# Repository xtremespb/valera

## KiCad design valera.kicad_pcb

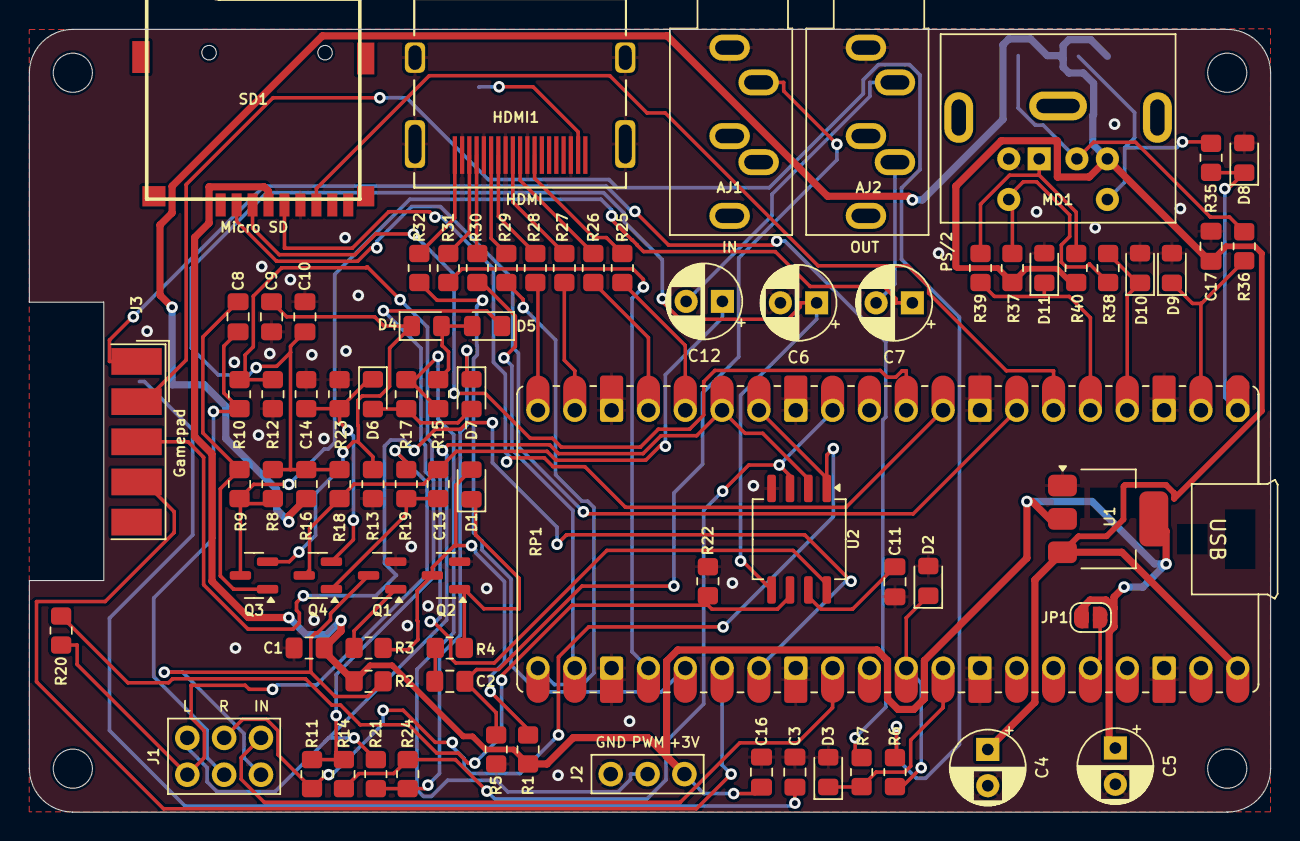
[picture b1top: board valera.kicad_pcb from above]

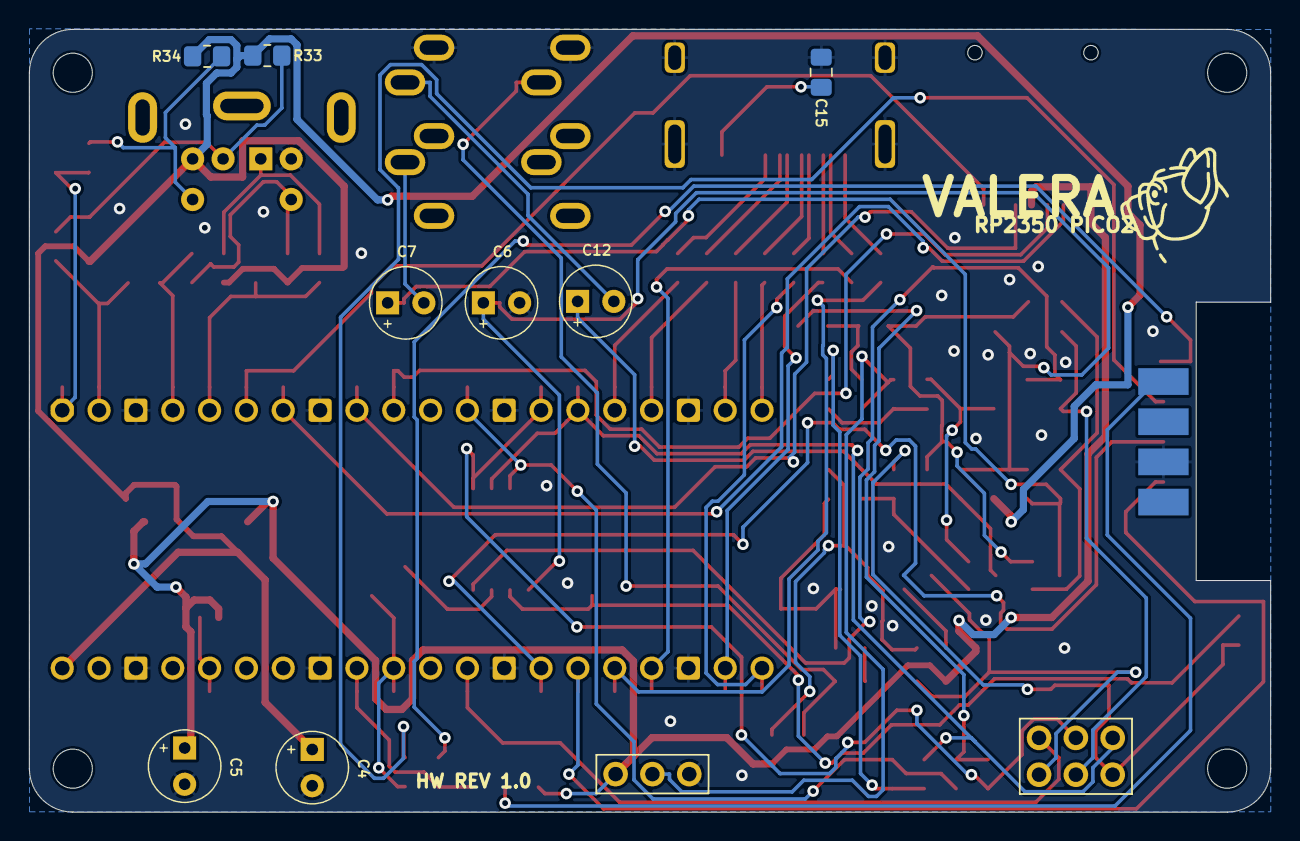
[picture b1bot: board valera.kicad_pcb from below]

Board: 2 copper layers, 85.6 x 54.0 mm, 88 parts (3 on the bottom side), 69 nets.

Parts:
AJ1: Audio IN; Jack_3.5mm
AJ2: Audio OUT; Jack_3.5mm
C1, C2, C9, C10, C15, C16: 100n; C_0805
C3: 0.1u; C_0805
C4, C5, C6, C7, C12: 10u; C_Radial
C8, C11: 1u; C_0805
C13: 1u; R_0805
C14: 100n; R_0805
C17: 10u; C_0805
D1, D4, D5, D6, D7: 4148; D_0805
D2, D3, D8, D9, D10, D11: 3V3; D_0805
H1, H2, H3, H4: MountingHole; MountingHole_2.7
HDMI1: HDMI
J1: Audio Jumpers; PinHeader_2x03
J2: PWM Jumper; PinHeader_1x03
J3: JOY-1; DSUB-9_Male_EdgeMount_P2.77mm
JP1: Enable 3V3; S_Jumper
MD1: Mini-DIN-6; Connector_Mini-DIN_Female_6Pin_2rows
Q1, Q2, Q3, Q4: BC850; Q_SOT-23
R1, R3, R4: 10K; R_0805
R2, R6, R7, R8, R12, R18, R22, R33, R34, R37: 1K; R_0805
R5, R13, R35, R36, R38, R39: 100R; R_0805
R9, R19: 100K*; R_0805
R10, R20: 20K; R_0805
R11, R21: 51R; R_0805
R14, R15, R17, R24: 200R; R_0805
R16: 10R; R_0805
R23: 100; R_0805
R25, R26, R27, R28, R29, R30, R31, R32: 270R; R_0805
R40: 1k; R_0805
RP1: Pico 2; Raspberry_Pi_Pico_SMT_THT_MOD_2
SD1: Micro_SD_Card; GCT-MEM2055-00-190-01-A
U1: AMS1117-3.3; SOT-223-3_TabPin2
U2: TDA1387T; SO_4x4

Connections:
+3V3: C1.1, C5.1, C16.2, J2.3, JP1.1 (A), R1.1, R2.1, SD1.4 (VDD), U1.2 (VO)
/3V3_EXT: JP1.2 (B), RP1.36 (3V3)
/AU_DATA: R14.2, R24.2, RP1.12 (GPIO9), U2.3 (DATA)
/AU_LRCK: J1.6, R21.2, RP1.15 (GPIO11), U2.2 (LRCK)
/AU_SCLK: J1.5, R11.2, RP1.14 (GPIO10), U2.1 (SCLK)
/Audio Out/+5VA: C6.1, C10.1, R8.1, R16.1, R18.1, U2.5 (VA)
/Audio Out/L: AJ2.T, C12.2
/Audio Out/R: AJ2.R, C7.2
/CLKN: R25.2, RP1.16 (GPIO12)
/CLKP: R26.2, RP1.17 (GPIO13)
/D0N: R27.2, RP1.19 (GPIO14)
/D0P: R28.2, RP1.20 (GPIO15)
/D1N: R29.2, RP1.21 (GPIO16)
/D1P: R30.2, RP1.22 (GPIO17)
/D2N: R31.2, RP1.24 (GPIO18)
/D2P: R32.2, RP1.25 (GPIO19)
/Gamepad/+5V: C3.1, J3.6
/Gamepad/J1_DATA: J3.2, R6.2
/Gamepad/J2_DATA: J3.1, R7.2
/HDMI/+5V: C15.1, HDMI1.18 (+5V)
/JOY_PIN1: D3.1 (K), R7.1, RP1.32 (GPIO27_ADC1)
/JOY_PIN2: D2.1 (K), R6.1, RP1.31 (GPIO26_ADC0)
/JOY_PIN3: J3.3, RP1.27 (GPIO21)
/JOY_PIN4: J3.4, RP1.26 (GPIO20)
/KB_CLK_3V: D10.1 (K), R38.2, RP1.4 (GPIO2)
/KB_DATA_3V: D11.1 (K), R39.2, RP1.5 (GPIO3)
/LEFT_OUT: C13.1, J1.1, R20.2
/LOAD_IN: J1.4, RP1.29 (GPIO22)
/LOAD_IN_D: J1.3, Q1.3 (C), R2.2
/MS_CLK_3V: D8.1 (K), R35.2, RP1.1 (GPIO0)
/MS_DATA_3V: D9.1 (K), R36.2, RP1.2 (GPIO1)
/PS2/PS/2 CLK: MD1.5, R37.2, R38.1
/PS2/PS/2 DATA: MD1.1, R39.1, R40.2
/PWM_EN: J2.2, R15.2, R17.1
/RIGHT_OUT: C8.1, J1.2, R10.2
/SD_CLK: RP1.9 (GPIO6), SD1.5 (CLK)
/SD_CS: RP1.7 (GPIO5), SD1.2 (DAT3/CD)
/SD_MISO: RP1.6 (GPIO4), SD1.7 (DAT0)
/SD_MOSI: RP1.10 (GPIO7), SD1.3 (CMD)
/Tape Loader/LOAD_IN: AJ1.T, C2.1, R5.1
GND: AJ1.S, AJ2.S, C1.2, C3.2, C4.2, C5.2, C6.2, C9.1, C10.2, C11.2, C14.1, C15.2, C16.1, C17.2, D2.2 (A), D3.2 (A), D8.2 (A), D9.2 (A), D10.2 (A), D11.2 (A), HDMI1.2 (G_D2), HDMI1.5 (G_D1), HDMI1.8 (G_D0), HDMI1.11 (G_CLK), HDMI1.17 (G_DDC/CEC), HDMI1.20 (SHIELD1), HDMI1.21 (SHIELD2), HDMI1.22 (SHIELD3), HDMI1.23 (SHIELD4), J2.1, J3.8, MD1.3, Q1.2 (E), Q2.2 (E), R5.2, R12.2, R13.2, R22.2, R23.2, RP1.3 (GND), RP1.8 (GND), RP1.13 (GND), RP1.18 (GND), RP1.23 (GND), RP1.28 (GND), RP1.33 (AGND), RP1.38 (GND), SD1.6 (VSS), U1.1 (GND), U2.4 (AGND)
unnamed: C2.2, R4.1
unnamed: D1.2 (A), Q2.3 (C), R1.2, R3.1
unnamed: D1.1 (K), Q2.1 (B), R4.2
unnamed: D4.2 (A), D5.2 (A), R15.1
unnamed: C9.2, D4.1 (K), Q3.2 (E), R13.1
unnamed: D5.1 (K), R11.1, R14.1
unnamed: D6.2 (A), D7.2 (A), R17.2
unnamed: C14.2, D6.1 (K), Q4.2 (E), R23.1
unnamed: D7.1 (K), R21.1, R24.1
unnamed: HDMI1.12 (CLKN), R25.1
unnamed: HDMI1.10 (CLKP), R26.1
unnamed: HDMI1.9 (D0N), R27.1
unnamed: HDMI1.7 (D0P), R28.1
unnamed: HDMI1.6 (D1N), R29.1
unnamed: HDMI1.4 (D1P), R30.1
unnamed: HDMI1.3 (D2N), R31.1
unnamed: HDMI1.1 (D2P), R32.1
unnamed: MD1.2, R33.2, R36.1
unnamed: MD1.6, R34.2, R35.1
unnamed: Q1.1 (B), R3.2
unnamed: C8.2, Q3.1 (B), R9.1
unnamed: C7.1, Q3.3 (C), R8.2, R9.2
unnamed: C13.2, Q4.1 (B), R19.1
unnamed: C12.1, Q4.3 (C), R18.2, R19.2
unnamed: R20.1, R22.1, U2.6 (A_LEFT)
unnamed: R10.1, R12.1, U2.8 (A_RIGHT)
unnamed: C11.1, U2.7 (FLT)
VBUS: C4.1, C17.1, MD1.4, R16.2, R33.1, R34.1, R37.1, R40.1, RP1.40 (VBUS), U1.3 (VI)

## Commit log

2025-01-07 HW Rev 1.0
2025-01-08 Minor updates to HW Rev 1.0
2025-01-08 Minor updates to schematics
